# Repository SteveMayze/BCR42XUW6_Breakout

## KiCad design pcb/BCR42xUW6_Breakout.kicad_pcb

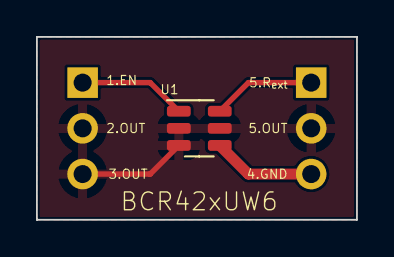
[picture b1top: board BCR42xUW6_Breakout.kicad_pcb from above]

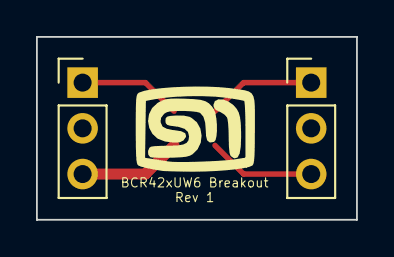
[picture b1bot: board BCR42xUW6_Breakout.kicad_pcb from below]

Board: 2 copper layers, 17.8 x 10.2 mm, 4 parts (3 on the bottom side), 4 nets.

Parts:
J1, J2: Conn_01x03_Male; PinHeader_1x03_P2.54mm_Vertical
Lg?: logo; MyBasic_rounded_50_1
U1: BCR42XUW6; SOT-23-6

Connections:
/EN: J1.1, U1.1 (EN)
/OUT: J1.2, J1.3, J2.2, U1.2 (OUT), U1.3 (OUT), U1.5 (OUT)
/R_{ext}: J2.1, U1.6 (R_{ext})
GND: J2.3, U1.4 (GND)

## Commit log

2022-05-29 Initial checkin of the breakout board
2022-06-06 Fixes the dimensions of the symbol
2023-02-06 Symbol update for DRC
